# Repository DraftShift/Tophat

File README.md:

#  Tophat 

&nbsp;&nbsp;&nbsp;&nbsp;&nbsp;&nbsp;
<a href="https://github.com/sponsors/DraftShift" target="_blank" alt="Sponsor Us">&color=rgb(191%2C%2057%2C%20137))</a>

## 🌐 Official Website

StealthChanger now has an official website!

👉 **https://stealthchanger.com** 

##
Currently there is only a simplified print it yourself version. This is meant for people not wanting to invest in more extrusions and side plates. you simply have to print the parts. and you can reuse your old top plate and corner pieces.

NOTE, a fully parametric design using extrusions is under design though it will take longer to finalise. The next design will have a bigger focus on adding things like lights, can wiring and other QOL / fancypants features.

### The current height is 200mm tall, check if this is good enough for your purposes!

## Printed part BOM
### 350 - 300
- 56x M3 heat inserts
- 24x M3x10mm SHCS
- 56x M3x8mm SHCS
- 24x M3 T-nut hammerhead

### 250
- 56x M3 heat inserts
- 24x M3x10mm SHCS
- 48x M3x8mm SHCS
- 16x M3 T-nut hammerhead

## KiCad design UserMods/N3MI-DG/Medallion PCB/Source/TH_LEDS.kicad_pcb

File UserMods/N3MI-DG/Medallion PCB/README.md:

# RGB PCB for Stealthchanger Medallion

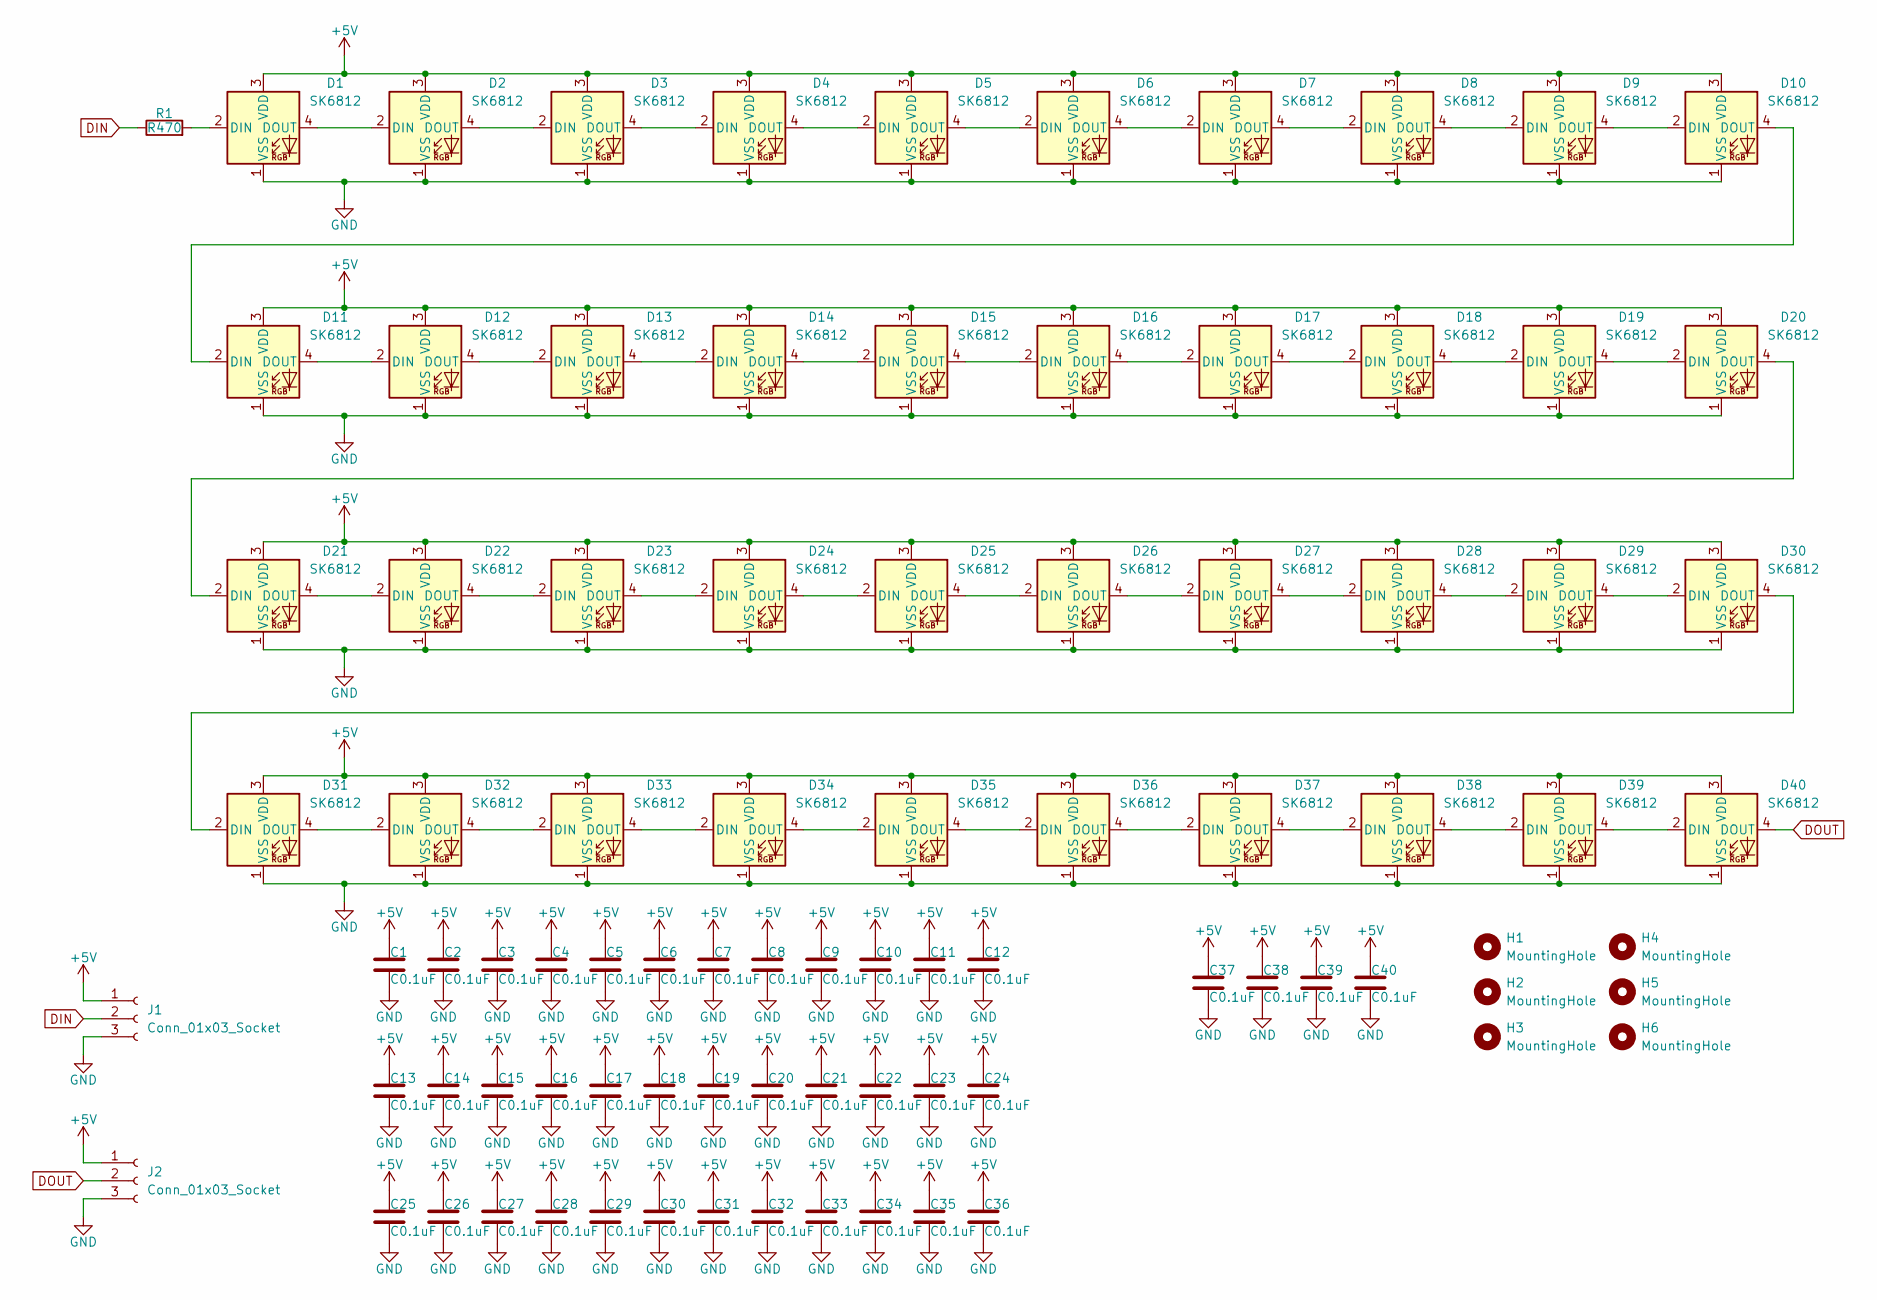
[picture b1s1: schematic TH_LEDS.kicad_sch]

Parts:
C1, C2, C3, C4, C5, C6, C7, C8, C9, C10, C11, C12, C13, C14, C15, C16, C17, C18, C19, C20, C21, C22, C23, C24, C25, C26, C27, C28, C29, C30, C31, C32, C33, C34, C35, C36, C37, C38, C39, C40: C0.1uF; C_0603_1608Metric
D1, D2, D3, D4, D5, D6, D7, D8, D9, D10, D11, D12, D13, D14, D15, D16, D17, D18, D19, D20, D21, D22, D23, D24, D25, D26, D27, D28, D29, D30, D31, D32, D33, D34, D35, D36, D37, D38, D39, D40: SK6812; LED_SK6812_PLCC4_5.0x5.0mm_P3.2mm
H1, H2, H3, H4, H5, H6: MountingHole; MountingHole_3.2mm_M3_DIN965_Pad
J1, J2: Conn_01x03_Socket; JST_XH_S3B-XH-SM4-TB_1x03-1MP_P2.50mm_Horizontal
R1: R470; R_0603_1608Metric

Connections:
+5V: C1.1, C2.1, C3.1, C4.1, C5.1, C6.1, C7.1, C8.1, C9.1, C10.1, C11.1, C12.1, C13.1, C14.1, C15.1, C16.1, C17.1, C18.1, C19.1, C20.1, C21.1, C22.1, C23.1, C24.1, C25.1, C26.1, C27.1, C28.1, C29.1, C30.1, C31.1, C32.1, C33.1, C34.1, C35.1, C36.1, C37.1, C38.1, C39.1, C40.1, D1.3 (VDD), D2.3 (VDD), D3.3 (VDD), D4.3 (VDD), D5.3 (VDD), D6.3 (VDD), D7.3 (VDD), D8.3 (VDD), D9.3 (VDD), D10.3 (VDD), D11.3 (VDD), D12.3 (VDD), D13.3 (VDD), D14.3 (VDD), D15.3 (VDD), D16.3 (VDD), D17.3 (VDD), D18.3 (VDD), D19.3 (VDD), D20.3 (VDD), D21.3 (VDD), D22.3 (VDD), D23.3 (VDD), D24.3 (VDD), D25.3 (VDD), D26.3 (VDD), D27.3 (VDD), D28.3 (VDD), D29.3 (VDD), D30.3 (VDD), D31.3 (VDD), D32.3 (VDD), D33.3 (VDD), D34.3 (VDD), D35.3 (VDD), D36.3 (VDD), D37.3 (VDD), D38.3 (VDD), D39.3 (VDD), D40.3 (VDD), J1.1, J2.1
DIN: J1.2, R1.1
DOUT: D40.4 (DOUT), J2.2
GND: C1.2, C2.2, C3.2, C4.2, C5.2, C6.2, C7.2, C8.2, C9.2, C10.2, C11.2, C12.2, C13.2, C14.2, C15.2, C16.2, C17.2, C18.2, C19.2, C20.2, C21.2, C22.2, C23.2, C24.2, C25.2, C26.2, C27.2, C28.2, C29.2, C30.2, C31.2, C32.2, C33.2, C34.2, C35.2, C36.2, C37.2, C38.2, C39.2, C40.2, D1.1 (VSS), D2.1 (VSS), D3.1 (VSS), D4.1 (VSS), D5.1 (VSS), D6.1 (VSS), D7.1 (VSS), D8.1 (VSS), D9.1 (VSS), D10.1 (VSS), D11.1 (VSS), D12.1 (VSS), D13.1 (VSS), D14.1 (VSS), D15.1 (VSS), D16.1 (VSS), D17.1 (VSS), D18.1 (VSS), D19.1 (VSS), D20.1 (VSS), D21.1 (VSS), D22.1 (VSS), D23.1 (VSS), D24.1 (VSS), D25.1 (VSS), D26.1 (VSS), D27.1 (VSS), D28.1 (VSS), D29.1 (VSS), D30.1 (VSS), D31.1 (VSS), D32.1 (VSS), D33.1 (VSS), D34.1 (VSS), D35.1 (VSS), D36.1 (VSS), D37.1 (VSS), D38.1 (VSS), D39.1 (VSS), D40.1 (VSS), J1.3, J2.3
unnamed: D1.2 (DIN), R1.2
unnamed: D1.4 (DOUT), D2.2 (DIN)
unnamed: D2.4 (DOUT), D3.2 (DIN)
unnamed: D3.4 (DOUT), D4.2 (DIN)
unnamed: D4.4 (DOUT), D5.2 (DIN)
unnamed: D5.4 (DOUT), D6.2 (DIN)
unnamed: D6.4 (DOUT), D7.2 (DIN)
unnamed: D7.4 (DOUT), D8.2 (DIN)
unnamed: D8.4 (DOUT), D9.2 (DIN)
unnamed: D9.4 (DOUT), D10.2 (DIN)
unnamed: D10.4 (DOUT), D11.2 (DIN)
unnamed: D11.4 (DOUT), D12.2 (DIN)
unnamed: D12.4 (DOUT), D13.2 (DIN)
unnamed: D13.4 (DOUT), D14.2 (DIN)
unnamed: D14.4 (DOUT), D15.2 (DIN)
unnamed: D15.4 (DOUT), D16.2 (DIN)
unnamed: D16.4 (DOUT), D17.2 (DIN)
unnamed: D17.4 (DOUT), D18.2 (DIN)
unnamed: D18.4 (DOUT), D19.2 (DIN)
unnamed: D19.4 (DOUT), D20.2 (DIN)
unnamed: D20.4 (DOUT), D21.2 (DIN)
unnamed: D21.4 (DOUT), D22.2 (DIN)
unnamed: D22.4 (DOUT), D23.2 (DIN)
unnamed: D23.4 (DOUT), D24.2 (DIN)
unnamed: D24.4 (DOUT), D25.2 (DIN)
unnamed: D25.4 (DOUT), D26.2 (DIN)
unnamed: D26.4 (DOUT), D27.2 (DIN)
unnamed: D27.4 (DOUT), D28.2 (DIN)
unnamed: D28.4 (DOUT), D29.2 (DIN)
unnamed: D29.4 (DOUT), D30.2 (DIN)
unnamed: D30.4 (DOUT), D31.2 (DIN)
unnamed: D31.4 (DOUT), D32.2 (DIN)
unnamed: D32.4 (DOUT), D33.2 (DIN)
unnamed: D33.4 (DOUT), D34.2 (DIN)
unnamed: D34.4 (DOUT), D35.2 (DIN)
unnamed: D35.4 (DOUT), D36.2 (DIN)
unnamed: D36.4 (DOUT), D37.2 (DIN)
unnamed: D37.4 (DOUT), D38.2 (DIN)
unnamed: D38.4 (DOUT), D39.2 (DIN)
unnamed: D39.4 (DOUT), D40.2 (DIN)

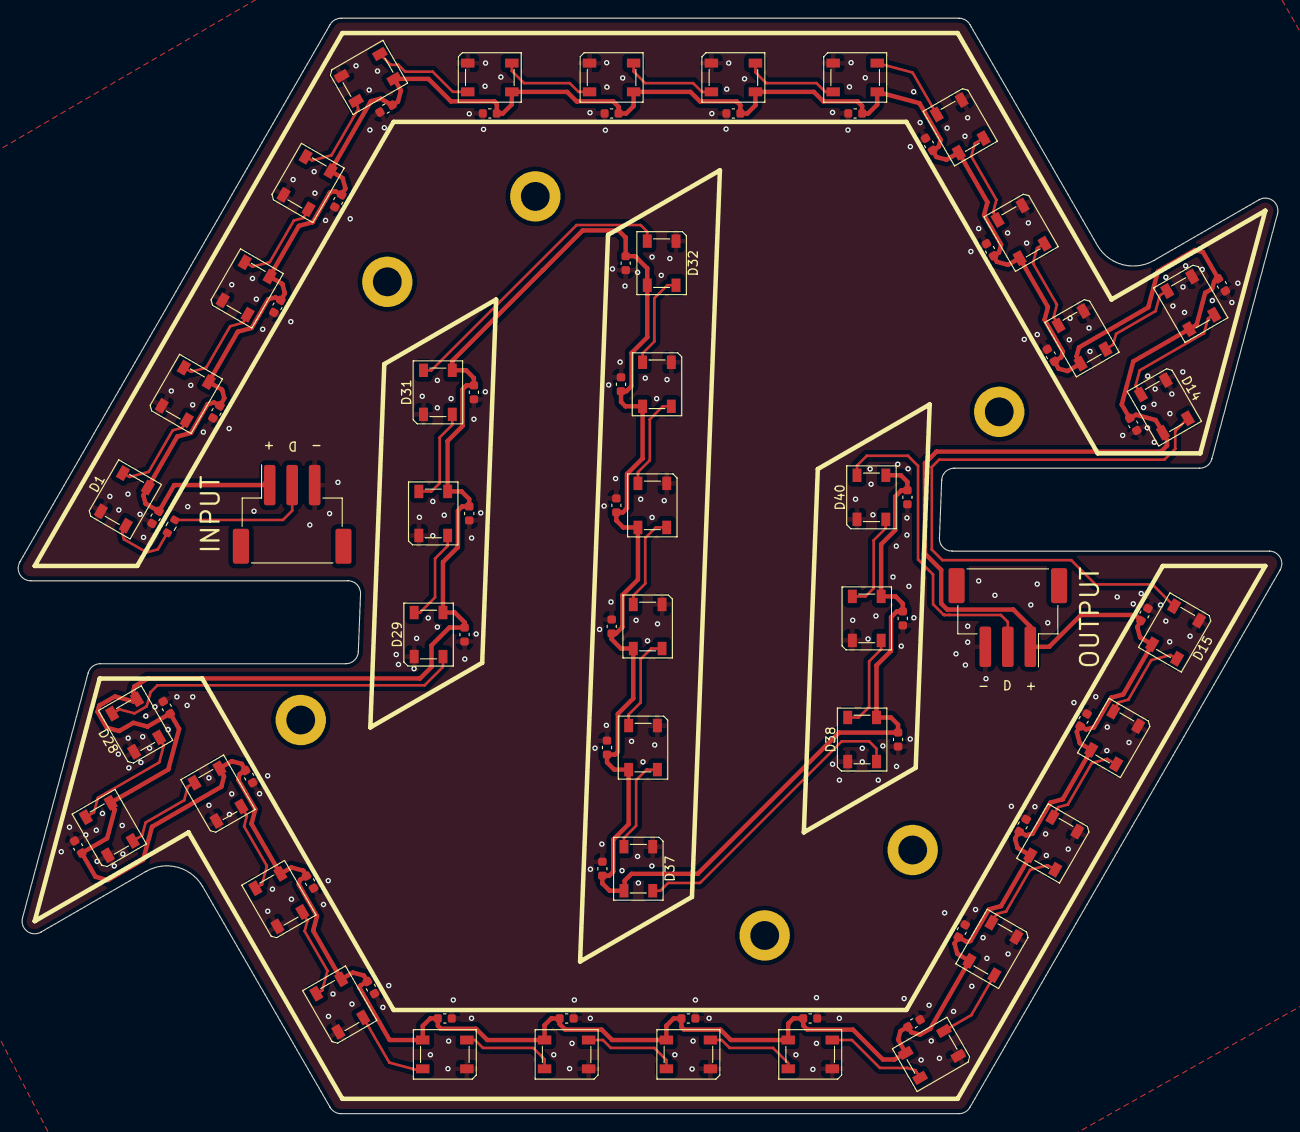
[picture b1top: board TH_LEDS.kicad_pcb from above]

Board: 2 copper layers, 140.5 x 121.8 mm, 89 parts (0 on the bottom side), 44 nets.

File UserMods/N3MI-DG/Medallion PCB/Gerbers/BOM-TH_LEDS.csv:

Comment,Designator,Footprint,LCSC,Quantity
C0.1uF,"C1,C10,C11,C12,C13,C14,C15,C16,C17,C18,C19,C2,C20,C21,C22,C23,C24,C25,C26,C27,C28,C29,C3,C30,C31,C32,C33,C34,C35,C36,C37,C38,C39,C4,C40,C5,C6,C7,C8,C9",C_0603_1608Metric,C14663,40
Conn_01x03_Socket,"J1,J2",JST_XH_S3B-XH-SM4-TB_1x03-1MP_P2.50mm_Horizontal,C161860,2
R470,R1,R_0603_1608Metric,C23179,1
SK6812,"D1,D10,D11,D12,D13,D14,D15,D16,D17,D18,D19,D2,D20,D21,D22,D23,D24,D25,D26,D27,D28,D29,D3,D30,D31,D32,D33,D34,D35,D36,D37,D38,D39,D4,D40,D5,D6,D7,D8,D9",LED_SK6812_PLCC4_5.0x5.0mm_P3.2mm,C5181320,40

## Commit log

2024-04-09 added stuff
2024-04-09 pushed new printed design and manual
2024-04-11 Update logo
2024-04-11 Fix location
2024-07-18 Added various logos for medallion
2024-07-18 Added CAD files for additional medallions
2024-08-06 Add links
2024-10-16 Update README.md
    Fixes #2
2025-10-08 Medallion PCB
2025-11-20 Merge pull request #4 from N3MI-DG/PCB
    Medallion PCB
2026-01-02 Add official website information to README
    Added section about the official website for StealthChanger.
2026-01-02 Update README with print version and design plans
    Added information about the simplified print version and future designs.
